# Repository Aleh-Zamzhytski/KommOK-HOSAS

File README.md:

# HOSAS Joystick Set

[Русская версия](#ru) · English

Two-stick controller set (HOSAS — Hands On Stick And Stick) for space flight simulators.
Eight analog axes: six for ship motion, two for camera control. Grips are 3D-printed,
boards are single-sided and suitable for home fabrication by the laser toner transfer
method (LTTM), controllers are STM32 Blue Pill or Arduino Pro Micro.

This document is the current build reference. Separate assembly documentation does not
exist yet; unfinished items are marked `TODO` and listed in [Known gaps](#known-gaps).

Video review (original sound in Russian): `TODO — YouTube link`

---

## 1. Overview

| Input | Axes | Buttons |
|---|---|---|
| Right grip | 4 | 2 |
| Left grip | 4 | 2 |

| Parameter | Value |
|---|---|
| Controller, current build | STM32 Blue Pill (STM32F103C8T6), USB Custom HID |
| Controller, earlier builds | Arduino Pro Micro (ATmega32U4), supported |
| Axis sensing | Potentiometers → ADC (DMA on STM32) |
| Centering | Return spring |
| Fastening | Wood screws into printed bosses |
| Host interface | USB, no driver installation |
| Desk mount | Welded 20×20 / 15×15 mm steel tube, M8 bolts |

## 2. Repository layout

```
body/                               3D models and print layouts
  Joystick_Base_v0.4.f3d / .step        base, editable source + STEP
  joystick_handle_v0.6.f3d / .step      grip, editable source + STEP
  Base_Print_Layout.3mf                 slicer project, base parts
  Left_Handle_Print_Layout.3mf          slicer project, left grip
  Right_Handle_Print_Layout.3mf         slicer project, right grip
electronics/
  joystick_v4_left/                     KiCad project + joystick_v4-Cu.svg (copper artwork)
  joystick_v4_right/                    KiCad project + joystick_v4-Cu.svg (copper artwork)
firmware/
  Arduino/HOSAS/HOSAS.ino               Pro Micro sketch
  STM32/CJoy/                           STM32CubeIDE project (CJoy.ioc, Core, USB_DEVICE)
  STM32/prebuilt/CJoy.bin               compiled firmware, flash-ready
BOM.md                                Bill of materials
```

One KiCad project per hand. Editable CAD is Fusion 360 (`.f3d`); `.step` is provided for
other CAD systems. STL files are not published — export from the STEP.

## 3. Parts and tools

Bill of materials: [BOM.md](BOM.md).

Tools: 3D printer; laser printer and glossy paper; iron; etching chemicals; carbide drill
bits; soldering iron and hot air; multimeter; crimp tool; ST-Link V2 for STM32 flashing.

## 4. Build

Sequence: print → PCB → assembly → firmware → verification. Test after each stage, not
after final assembly; faults are cheaper to find early.

### 4.1 Printing

Print the four slicer projects in `body/` — 2x base, left grip, right grip. Parts are already
arranged with supports. Scale 100 %: potentiometer seats and screw bosses are
dimension-critical.

| Parameter | Value |
|---|---|
| Material | eSun PLA+ |
| Nozzle | 0.4 |
| Slicer | Orca Slicer v2.4.1 |

### 4.2 PCB fabrication (LTTM)

**Current PCB design is for STM32 only.**
`TODO add Arduino Pro Micro PCB design`
Artwork: `electronics/joystick_v4_*/joystick_v4-Cu.svg` (copper layer).
Project files: `.kicad_pro`, `.kicad_sch`, `.kicad_pcb` — KiCad 9.0.

Home fabrication is recommended for a first prototype: a fab-house order adds weeks of
lead time before a layout error becomes apparent.

1. **Print the artwork** on glossy paper with a laser printer, **it is already mirrored**, at 1:1 scale.
   Verify the scale against a known 2.54 mm header pitch before transfer.
2. **Prepare the laminate:** wet 1000-grit abrasive, then degrease with alcohol.
3. **Transfer:** iron near maximum (cotton setting), toner side down, about two minutes
   with firm, even pressure.
4. **Remove the paper:** soak in hot soapy water for 30 minutes, then roll the paper off
   with the fingers under water. Toner remaining on copper indicates the correct
   temperature; smeared toner means too hot, toner left on paper means too cold.
5. **Etch:** 100 ml hydrogen peroxide + 30 g citric acid + 5 g sodium chloride. Keep the
   vessel on a water bath or other mild heat source and agitate periodically. Clearing of
   the copper between tracks takes 20–30 minutes.
6. **Finish:** strip the toner with fine abrasive, drill with carbide bits (standard bits
   tear the tracks), trim the board to size.
7. **Tin and solder:** rosin or no-clean flux only; acid fluxes are not acceptable.
   Through-hole components from the solder side, SMD on the component side with hot air.
   A double-sided board is made as two single-sided boards joined by wire links.
8. **Verify:** check every track for continuity and every adjacent pair for shorts with a
   multimeter. Use crimped DuPont connectors for detachable wiring.

Read [Safety](#5-safety) before etching.

### 4.3 Mechanical assembly

Detailed instructions: `TODO`. Current sequence:

1. Mount the potentiometers in their designed seats and check alignment over the full
   travel of each axis before fixing them.
2. Fasten the boards and mechanical parts with wood screws into the printed bosses.
   Plastic threads tolerate limited torque; overtightening breaks them.
3. Fit the return spring under tension. Confirm free travel and reliable centering of
   both axes before closing the grip.
4. Wire the axes and buttons according to the schematic, then verify direction and
   endpoint values on the host before final closure.

### 4.4 Firmware

**Arduino Pro Micro** — `firmware/Arduino/HOSAS/HOSAS.ino`

Open the sketch in Arduino IDE, select board `Arduino Micro`, install 
https://github.com/MHeironimus/ArduinoJoystickLibrary, upload, then verify in the host joystick panel.

**STM32 Blue Pill** — `firmware/STM32/CJoy/`

STM32CubeIDE project generated from `CJoy.ioc`. Target STM32F103C8Tx, linker script
`STM32F103C8TX_FLASH.ld`. USB class: Custom HID; the report descriptor is defined in
`USB_DEVICE/App/usbd_custom_hid_if.c`. Axes are read by ADC with DMA
(`Core/Src/adc.c`, `Core/Src/dma.c`), buttons through GPIO.

- Build: import the project into STM32CubeIDE and build.
- Flash without building: `firmware/STM32/prebuilt/CJoy.bin`.
- Upload: ST-Link V2 over SWD (SWDIO, SWCLK, GND, 3V3), or the factory USART1 bootloader
  with BOOT0 = 1 using STM32CubeProgrammer. Flash address `0x08000000`.
- Axis limits, inversion, and deadzone: `TODO — document the constants in Core/Src/main.c`.

The Blue Pill costs about half as much as the Pro Micro and offers higher performance;
the flashing procedure is more involved.

### 4.5 Verification and binding

1. Confirm that both sticks enumerate as separate USB devices.
2. Open the host joystick panel (Windows: `joy.cpl`) and check all axes and all
   buttons: full range, stable center, no jitter, correct direction.
3. Assign the axes in the simulator, invert where required, apply a deadzones,
   and set response curves for the translation axes.

## 5. Safety

Respiratory and eye protection are required when abrading copper laminate and when
etching; work in a ventilated area. Welding and abrasive cutting require the corresponding
protective equipment.

Spent etchant must not be discharged into the drain. Neutralise it with iron filings or
steel offcuts; decant only the clear liquid after neutralisation and dispose of the solid
residue as household waste.

The project is provided "as is", without warranty. Fabrication and use are undertaken at
the operator's own risk.

## 6. Desk mount

The mount holds the grip at elbow height and leaves the keyboard and mouse area free.
Construction: 20×20 and 15×15 mm steel tube, cut, welded, roller-painted, with felt pads on
all desk contact surfaces to prevent slipping and scratching.

Cut list and drawings: `TODO — not published yet`.

## Known gaps

- Step-by-step mechanical assembly instructions.
- Desk mount cut list and drawings.
- Third-revision defects and planned changes.

Corrections and additions are welcome through Issues.

## License

| Scope | License |
|---|---|
| Firmware (`firmware/`) | Apache License 2.0 |
| CAD models, PCB designs, documentation, media | CC BY 4.0 |

Copying, modification, and redistribution, including commercial use, are permitted.
Firmware redistribution requires retention of the LICENSE and NOTICE files and a notice
stating that files were modified. Redistribution of design files requires credit, a link
to this repository, a link to the license, and an indication of changes.

> Based on the HOSAS Joystick project by Aleh-Zamzhytski and Kommande —
> https://github.com/Aleh-Zamzhytski/KommOK-HOSAS (hardware: CC BY 4.0, firmware: Apache-2.0).

Attribution on physical builds, photographs, and videos is appreciated but not required.
Third-party components under `firmware/STM32/CJoy/Drivers` and `Middlewares` retain their
own licenses (see the `LICENSE.txt` files in those directories).

---

## Комплект HOSAS Джойстиков

[English version](#hosas-joystick-set) · Русский

Комплект из двух джойстиков (HOSAS — Hands On Stick And Stick) для космических
симуляторов. Восемь аналоговых осей: шесть на движение корабля, две на камеру.
Рукояти печатаются на 3D-принтере, платы односторонние и изготавливаются дома по
лазерно-утюжной технологии (ЛУТ), контроллеры — STM32 Blue Pill или Arduino Pro Micro.

Видеообзор: `TODO — ссылка на YouTube`

Раздел повторяет английскую версию выше. При расхождении актуальна английская.

### 1. Обзор

| Орган управления | Оси | Кнопки |
|---|---|---|
| Правый джойстик | 4 | 2 |
| Левый джойстик | 4 | 2 |

| Параметр | Значение |
|---|---|
| Контроллер, текущая версия | STM32 Blue Pill (STM32F103C8T6), USB Custom HID |
| Контроллер, ранние версии | Arduino Pro Micro (ATmega32U4), поддерживается |
| Оси | Потенциометры → АЦП (DMA на STM32) |
| Возврат в центр | Возвратная пружина |
| Крепёж | Саморезы по дереву в печатные колодцы |
| Интерфейс | USB, установка драйверов не требуется |
| Крепление к столу | Сварная профильная труба 20×20 / 15×15 мм, болты М8 |

### 2. Файлы репозитория

Структура приведена в [английском разделе](#2-repository-layout): имена файлов и каталогов
от языка не зависят.

Один проект KiCad на каждую руку. Редактируемые модели — Fusion 360 (`.f3d`), `.step`
предоставлен для других CAD-систем. STL можно получить экспортом из STEP.

### 3. Детали и инструмент

Спецификация деталей: [BOM.md](BOM.md).

Инструмент: 3D-принтер; лазерный принтер и глянцевая бумага; утюг; реактивы для травления;
свёрла из карбида вольфрама; паяльник и фен; мультиметр; кримпер; ST-Link V2 для прошивки STM32.

### 4. Сборка

Последовательность: печать → плата → сборка → прошивка → проверка. Контроль выполняется
после каждого этапа, а не после окончательной сборки: так дефекты обходятся дешевле.

#### 4.1 Печать

Печатаются четыре набора деталей из трёх файлов в `body/`: база — дважды (по одной на
каждый джойстик), левый джойстик, правый джойстик. Детали уже расставлены с поддержками.
Масштаб 100 %: посадочные места потенциометров и колодцы под саморезы критичны к размерам.

| Параметр | Значение |
|---|---|
| Материал | eSun PLA+ |
| Сопло | 0,4 мм |
| Слайсер | Orca Slicer v2.4.1 |

#### 4.2 Изготовление платы (ЛУТ)

Текущая разводка рассчитана только на STM32. `TODO — добавить плату под Arduino Pro Micro`

Картинка для перевода на текстолит: `electronics/joystick_v4_*/joystick_v4-Cu.svg`.
Файлы проекта: `.kicad_pro`, `.kicad_sch`, `.kicad_pcb` — KiCad 9.0.

Для первого прототипа рекомендуется домашнее изготовление: заказ на фабрике добавляет
недели ожидания, прежде чем обнаружится ошибка в разводке.

1. **Печать рисунка** на глянцевой бумаге лазерным принтером, масштаб 1:1.
   Рисунок **уже отзеркален**, повторно зеркалить не нужно. Перед переносом проверить
   масштаб по заведомо известному шагу выводов 2,54 мм.
2. **Подготовка текстолита:** мокрая наждачная бумага P1000, затем обезжиривание IPA спиртом.
3. **Перенос:** утюг почти на максимум (режим «хлопок»), тонером вниз, около двух минут
   с равномерным прижимом.
4. **Снятие бумаги:** замачивание в горячей воде с мылом на 30 минут, затем скатывание
   бумаги пальцами под водой. Тонер остался на меди — температура выбрана верно;
   расплылся — утюг перегрет; остался на бумаге — недогрет.
5. **Травление:** 100 мл перекиси водорода + 30 г лимонной кислоты + 5 г поваренной соли.
   Ёмкость на водяной бане или другом слабом нагреве, периодически помешивать.
   Медь между дорожками уходит за 20–30 минут.
6. **Финиш:** снять тонер мелкой наждачкой, сверлить карбидным сверлом (обычное рвёт
   дорожки), обрезать плату по размеру.
7. **Лужение и пайка:** только канифоль или безотмывочный флюс; кислотные флюсы
   недопустимы. DIP-компоненты — с обратной стороны, SMD — феном с лицевой.
   Двусторонняя плата изготавливается как две односторонние, соединённые проволочными
   перемычками.
8. **Контроль:** прозвонить мультиметром каждую дорожку на обрыв и каждую соседнюю пару
   на замыкание. Разъёмные соединения — обжатые контакты DuPont.

Перед травлением прочитать [раздел 5](#5-безопасность).

#### 4.3 Механическая сборка

Подробная инструкция: `TODO`. Текущая последовательность:

1. Установить потенциометры в посадочные места и проверить показания для каждой оси до окончательного крепления.
2. Крепить платы и механику саморезами по дереву в печатные колодцы. Резьба в пластике
   держит ограниченный момент; перетяжка её срывает.
3. Установить возвратную пружину с натягом. До финальной сборки рукояти убедиться в свободном
   ходе и надёжном возврате обеих осей в центр.
4. Развести оси и кнопки по схеме, затем проверить направление и крайние значения
   на компьютере.

#### 4.4 Прошивка

**Arduino Pro Micro** — `firmware/Arduino/HOSAS/HOSAS.ino`

Открыть скетч в Arduino IDE, выбрать плату `Arduino Micro`, установить библиотеку
[ArduinoJoystickLibrary](https://github.com/MHeironimus/ArduinoJoystickLibrary),
загрузить, проверить в панели игровых устройств.

**STM32 Blue Pill** — `firmware/STM32/CJoy/`

Проект STM32CubeIDE, сгенерированный из `CJoy.ioc`. Плата STM32F103C8Tx, linker script
`STM32F103C8TX_FLASH.ld`. Класс USB — Custom HID; дескриптор отчёта задан в
`USB_DEVICE/App/usbd_custom_hid_if.c`. Оси читаются АЦП с DMA (`Core/Src/adc.c`,
`Core/Src/dma.c`), кнопки — через GPIO.

- Сборка: импортировать проект в STM32CubeIDE и собрать.
- Прошивка без сборки: `firmware/STM32/prebuilt/CJoy.bin`.
- Загрузка: ST-Link V2 по SWD (SWDIO, SWCLK, GND, 3V3) либо штатный загрузчик USART1
  при BOOT0 = 1 через STM32CubeProgrammer. Адрес `0x08000000`.
- Пределы осей, инверсия и мёртвая зона: `TODO — описать константы в Core/Src/main.c`.

Blue Pill примерно вдвое дешевле Pro Micro при большей производительности; процедура
прошивки сложнее.

#### 4.5 Проверка и назначение осей

1. Убедиться, что оба джойстика определяются как отдельные USB-устройства.
2. Открыть панель игровых устройств (Windows: `joy.cpl`) и проверить все оси и кнопки:
   полный диапазон, устойчивый центр, отсутствие дрожания, верное направление.
3. Назначить оси в симуляторе, при необходимости инвертировать, задать мёртвые зоны
   и кривые отклика для осей смещения.

### 5. Безопасность

При зачистке текстолита и травлении обязательны респиратор и защитные очки; работать
в проветриваемом помещении. Сварка и абразивная резка требуют соответствующих средств
защиты.

Отработанный раствор не сливается в канализацию. Он нейтрализуется железными опилками
или стальными обрезками; после нейтрализации сливается только прозрачная жидкость,
твёрдый остаток утилизируется как бытовой отход.

Проект предоставляется «как есть», без гарантий. Изготовление и использование —
на риск исполнителя.

### 6. Крепление к столу

Крепление удерживает рукоять на уровне локтя и оставляет свободными место на столе для клавиатуры и мыши.
Конструкция: профильная труба 20×20 и 15×15 мм, резка, сварка, окраска валиком,
войлочные накладки на всех площадках, касающихся стола, — против скольжения и царапин.
Крепление изготавливается отдельно для каждого джойстика.

Раскрой и чертежи: `TODO — ещё не опубликованы`.

### Известные пробелы

- Пошаговая инструкция по механической сборке.
- Раскрой и чертежи крепления к столу.
- Дефекты третьей ревизии и планируемые изменения.

Исправления и дополнения принимаются через Issues.

### Лицензия

| Область | Лицензия |
|---|---|
| Прошивка (`firmware/`) | Apache License 2.0 |
| 3D-модели, платы, документация, медиа | CC BY 4.0 |

Копирование, изменение и распространение, включая коммерческое использование, разрешены.
При распространении прошивки обязательны сохранение файлов LICENSE и NOTICE и указание
на внесённые изменения. При распространении файлов конструкции обязательны указание
авторства, ссылка на репозиторий, ссылка на лицензию и отметка об изменениях.
Полные условия — в [английском разделе](#license).

> Based on the HOSAS Joystick project by Aleh-Zamzhytski and Kommande —
> https://github.com/Aleh-Zamzhytski/KommOK-HOSAS (hardware: CC BY 4.0, firmware: Apache-2.0).

Указание авторства на физических сборках, фотографиях и видео приветствуется,
но не обязательно.

Сторонние компоненты в `firmware/STM32/CJoy/Drivers` и `Middlewares` сохраняют
собственные лицензии (см. файлы `LICENSE.txt` в этих каталогах).

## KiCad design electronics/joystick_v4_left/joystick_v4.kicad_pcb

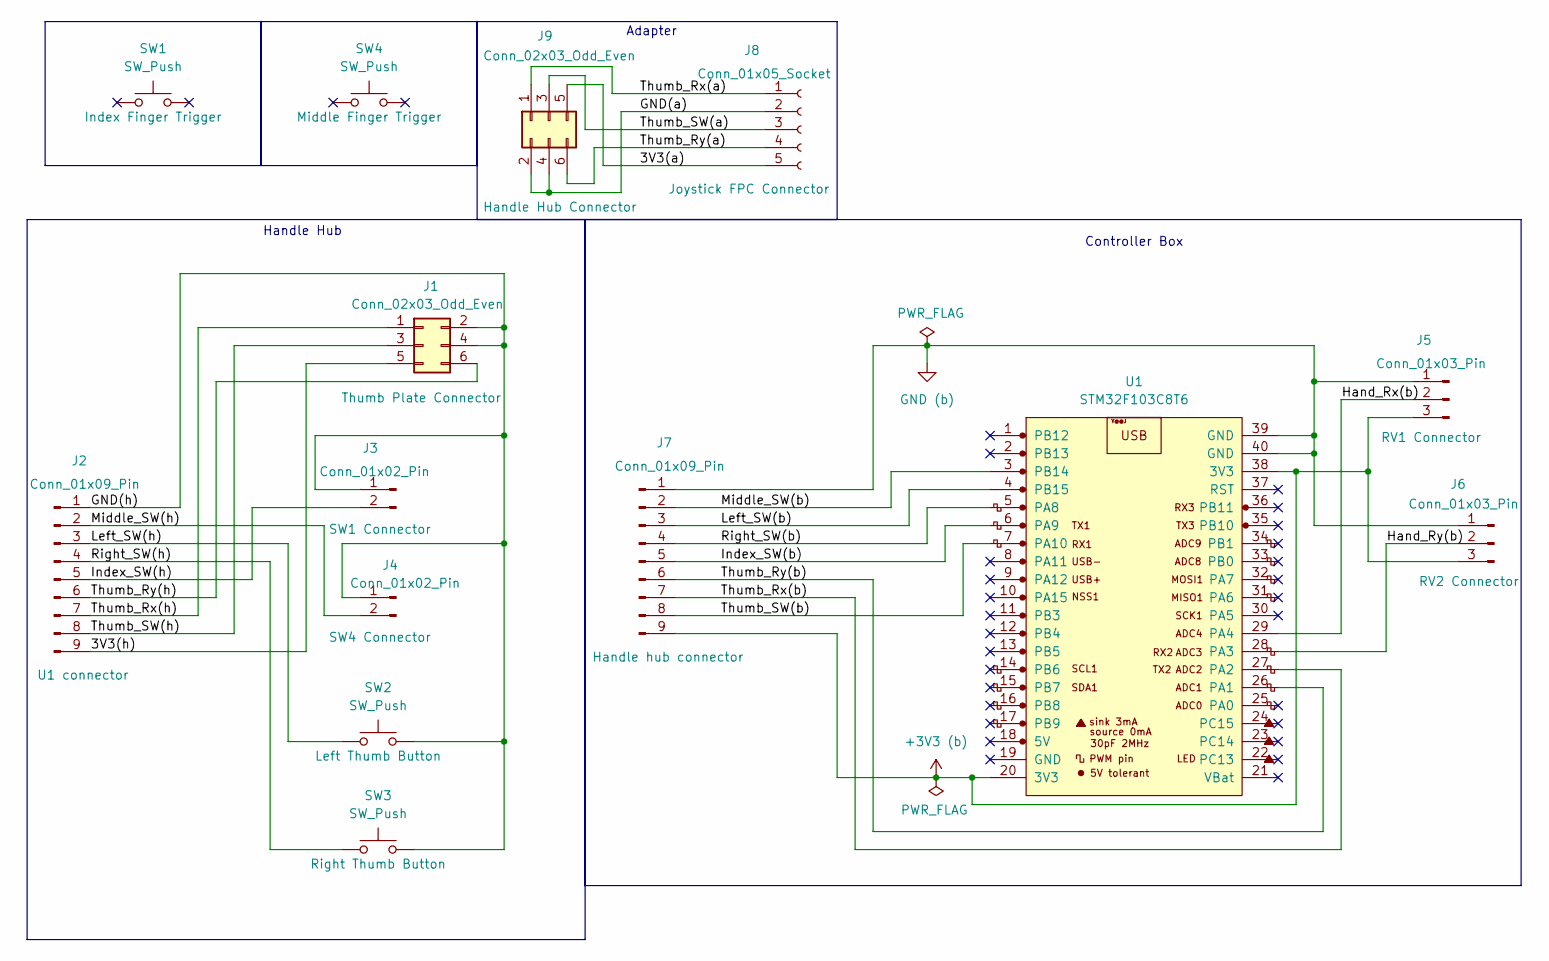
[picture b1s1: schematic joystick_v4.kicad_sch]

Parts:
J1, J9: Conn_02x03_Odd_Even; PinHeader_2x03_P2.54mm_Vertical
J2, J7: Conn_01x09_Pin; PinHeader_1x09_P2.54mm_Vertical
J3, J4: Conn_01x02_Pin; PinHeader_1x02_P2.54mm_Vertical
J5, J6: Conn_01x03_Pin; PinHeader_1x03_P2.54mm_Vertical
J8: Conn_01x05_Socket; TE_0-1734839-5_1x05-1MP_P0.5mm_Horizontal
SW1, SW2, SW3, SW4: SW_Push; SW_PUSH_6mm_H5mm
U1: STM32F103C8T6; YAAJ_BluePill_1

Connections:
+3V3 (b): J5.3, J6.3, J7.9, U1.20 (3V3), U1.38 (3V3)
/3V3(a): J8.5, J9.5
/3V3(h): J1.5, J2.9
/GND(a): J8.2, J9.2, J9.4
/GND(h): J1.2, J1.4, J2.1, J3.1, J4.1, SW2.2, SW3.2
/Hand_Rx(b): J5.2, U1.29 (PA4)
/Hand_Ry(b): J6.2, U1.28 (PA3)
/Index_SW(b): J7.5, U1.6 (PA9)
/Index_SW(h): J2.5, J3.2
/Left_SW(b): J7.3, U1.4 (PB15)
/Left_SW(h): J2.3, SW2.1
/Middle_SW(b): J7.2, U1.3 (PB14)
/Middle_SW(h): J2.2, J4.2
/Right_SW(b): J7.4, U1.5 (PA8)
/Right_SW(h): J2.4, SW3.1
/Thumb_Rx(a): J8.1, J9.1
/Thumb_Rx(b): J7.7, U1.27 (PA2)
/Thumb_Rx(h): J1.1, J2.7
/Thumb_Ry(a): J8.4, J9.6
/Thumb_Ry(b): J7.6, U1.26 (PA1)
/Thumb_Ry(h): J1.6, J2.6
/Thumb_SW(a): J8.3, J9.3
/Thumb_SW(b): J7.8, U1.7 (PA10)
/Thumb_SW(h): J1.3, J2.8
GND (b): J5.1, J6.1, J7.1, U1.39 (GND), U1.40 (GND)

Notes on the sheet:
Handle Hub
Controller Box
Adapter

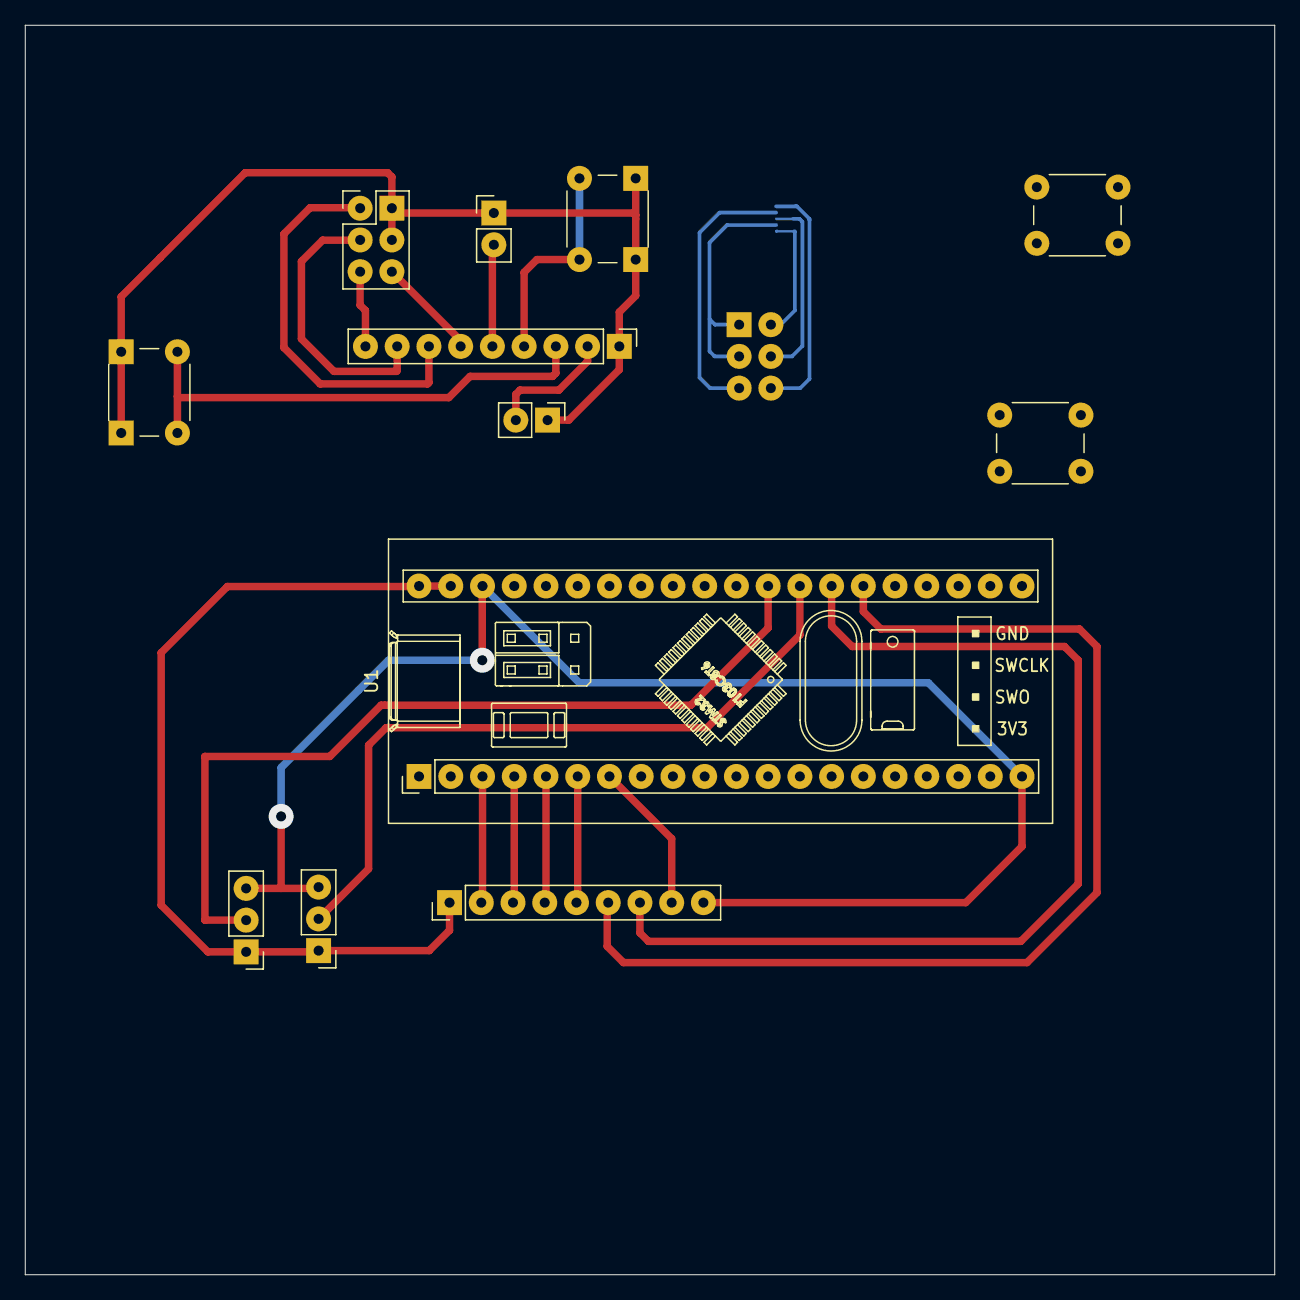
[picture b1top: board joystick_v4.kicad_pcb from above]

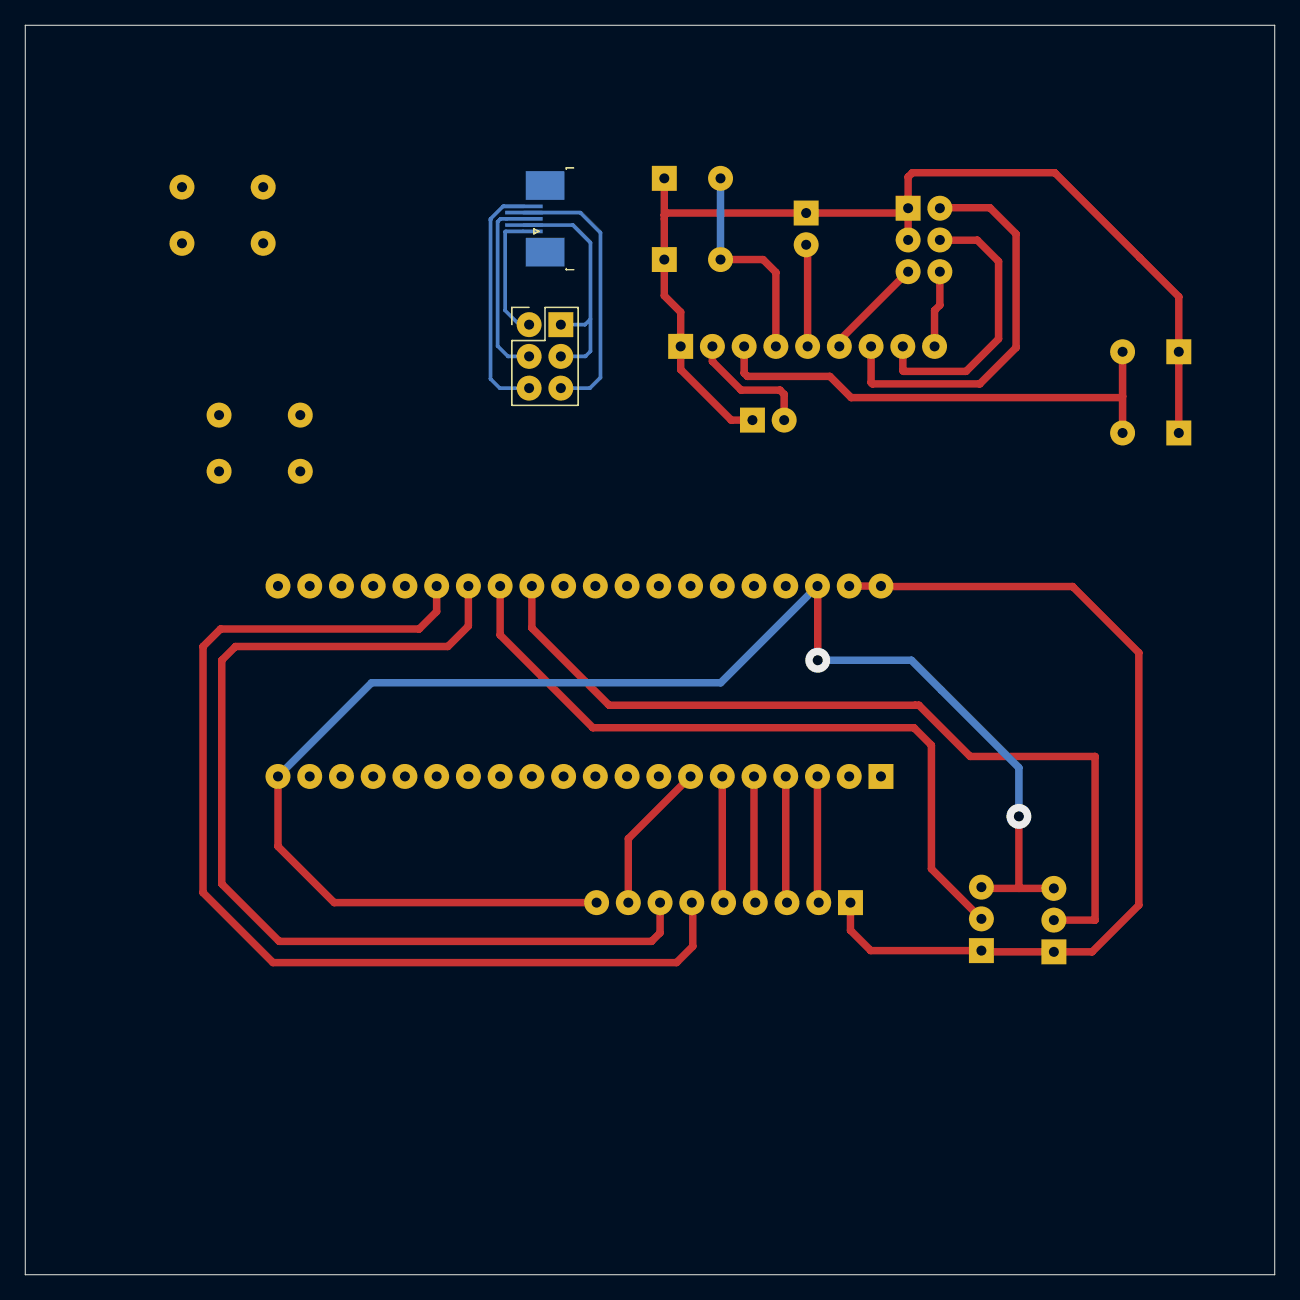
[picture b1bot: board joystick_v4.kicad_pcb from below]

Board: 2 copper layers, 100.0 x 100.0 mm, 14 parts (2 on the bottom side), 25 nets.

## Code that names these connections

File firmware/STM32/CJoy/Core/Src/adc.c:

/* USER CODE BEGIN Header */
/**
  ******************************************************************************
  * @file    adc.c
  * @brief   This file provides code for the configuration
  *          of the ADC instances.
  ******************************************************************************
  * @attention
  *
  * Copyright (c) 2025 STMicroelectronics.
  * All rights reserved.
  *
  * This software is licensed under terms that can be found in the LICENSE file
  * in the root directory of this software component.
  * If no LICENSE file comes with this software, it is provided AS-IS.
  *
  ******************************************************************************
  */
/* USER CODE END Header */
/* Includes ------------------------------------------------------------------*/
#include "adc.h"

/* USER CODE BEGIN 0 */
volatile uint16_t adc_dma_buffer[ADC_BUFFER_SIZE];
volatile uint32_t adc_filtered_values[ADC_CHANNELS] = {0};
volatile uint8_t adc_data_ready = 0;

typedef struct
{
  uint16_t buffer[FILTER_WINDOW];
  uint8_t index;
  uint32_t sum;
} MovingAverageFilter;

MovingAverageFilter adc_filters[ADC_CHANNELS] = {0};

void ADC_Filter_Init(void)
{
  for (int ch = 0; ch < ADC_CHANNELS; ch++)
  {
    for (int i = 0; i < FILTER_WINDOW; i++)
    {
      adc_filters[ch].buffer[i] = 0;
    }
    adc_filters[ch].index = 0;
    adc_filters[ch].sum = 0;
  }
}

uint16_t ADC_Apply_Moving_Average(uint8_t channel, uint16_t new_value)
{
  MovingAverageFilter *filter = &adc_filters[channel];

  filter->sum -= filter->buffer[filter->index];
  filter->buffer[filter->index] = new_value;
  filter->sum += new_value;

  filter->index = (filter->index + 1) % FILTER_WINDOW;

  return (uint16_t)(filter->sum / FILTER_WINDOW);
}

void ADC_Start_DMA_Conversion(void)
{
  ADC_Filter_Init();
  if (HAL_ADC_Start_DMA(&hadc1, (uint32_t *)adc_dma_buffer, ADC_BUFFER_SIZE) != HAL_OK)
  {
    Error_Handler();
  }
}

uint16_t ADC_GetFilteredValue(uint8_t channel)
{
  if (channel < ADC_CHANNELS)
  {
    return (uint16_t)adc_filtered_values[channel];
  }
  return 0;
}


void HAL_ADC_ConvHalfCpltCallback(ADC_HandleTypeDef *hadc)
{
  if (hadc->Instance == ADC1)
  {
    for (int i = 0; i < ADC_BUFFER_SIZE / 2; i += ADC_CHANNELS)
    {
      for (int ch = 0; ch < ADC_CHANNELS; ch++)
      {
        uint16_t raw_value = adc_dma_buffer[i + ch];
        uint16_t filtered = ADC_Apply_Moving_Average(ch, raw_value);
        adc_filtered_values[ch] = filtered;
      }
    }
  }
}

void HAL_ADC_ConvCpltCallback(ADC_HandleTypeDef *hadc)
{
  if (hadc->Instance == ADC1)
  {

    for (int i = ADC_BUFFER_SIZE / 2; i < ADC_BUFFER_SIZE; i += ADC_CHANNELS)
    {
      for (int ch = 0; ch < ADC_CHANNELS; ch++)
      {
        uint16_t raw_value = adc_dma_buffer[i + ch];
        uint16_t filtered = ADC_Apply_Moving_Average(ch, raw_value);
        adc_filtered_values[ch] = filtered;
      }
    }
    adc_data_ready = 1;
  }
}
/* USER CODE END 0 */

ADC_HandleTypeDef hadc1;
DMA_HandleTypeDef hdma_adc1;

/* ADC1 init function */
void MX_ADC1_Init(void)
{

  /* USER CODE BEGIN ADC1_Init 0 */

  /* USER CODE END ADC1_Init 0 */

  ADC_ChannelConfTypeDef sConfig = {0};

  /* USER CODE BEGIN ADC1_Init 1 */

  /* USER CODE END ADC1_Init 1 */

  /** Common config
  */
  hadc1.Instance = ADC1;
  hadc1.Init.ScanConvMode = ADC_SCAN_ENABLE;
  hadc1.Init.ContinuousConvMode = ENABLE;
  hadc1.Init.DiscontinuousConvMode = DISABLE;
  hadc1.Init.ExternalTrigConv = ADC_SOFTWARE_START;
  hadc1.Init.DataAlign = ADC_DATAALIGN_RIGHT;
  hadc1.Init.NbrOfConversion = 4;

  if (HAL_ADC_Init(&hadc1) != HAL_OK)
  {
    Error_Handler();
  }

  /** Configure Regular Channel
  */
  sConfig.Channel = ADC_CHANNEL_1;
  sConfig.Rank = ADC_REGULAR_RANK_1;
  sConfig.SamplingTime = ADC_SAMPLETIME_239CYCLES_5;
  if (HAL_ADC_ConfigChannel(&hadc1, &sConfig) != HAL_OK)
  {
    Error_Handler();
  }

  /** Configure Regular Channel
  */
  sConfig.Channel = ADC_CHANNEL_2;
  sConfig.Rank = ADC_REGULAR_RANK_2;
  sConfig.SamplingTime = ADC_SAMPLETIME_239CYCLES_5;
  if (HAL_ADC_ConfigChannel(&hadc1, &sConfig) != HAL_OK)
  {
    Error_Handler();
  }

  /** Configure Regular Channel
  */
  sConfig.Channel = ADC_CHANNEL_3;
  sConfig.Rank = ADC_REGULAR_RANK_3;
  sConfig.SamplingTime = ADC_SAMPLETIME_239CYCLES_5;
  if (HAL_ADC_ConfigChannel(&hadc1, &sConfig) != HAL_OK)
  {
    Error_Handler();
  }

  /** Configure Regular Channel
  */
  sConfig.Channel = ADC_CHANNEL_4;
  sConfig.Rank = ADC_REGULAR_RANK_4;
  sConfig.SamplingTime = ADC_SAMPLETIME_239CYCLES_5;
  if (HAL_ADC_ConfigChannel(&hadc1, &sConfig) != HAL_OK)
  {
    Error_Handler();
  }
  /* USER CODE BEGIN ADC1_Init 2 */

  /* USER CODE END ADC1_Init 2 */

}

void HAL_ADC_MspInit(ADC_HandleTypeDef* adcHandle)
{

  GPIO_InitTypeDef GPIO_InitStruct = {0};
  if(adcHandle->Instance==ADC1)
  {
  /* USER CODE BEGIN ADC1_MspInit 0 */

  /* USER CODE END ADC1_MspInit 0 */
    /* ADC1 clock enable */
    __HAL_RCC_ADC1_CLK_ENABLE();

    __HAL_RCC_GPIOA_CLK_ENABLE();
    /**ADC1 GPIO Configuration
    PA1     ------> ADC1_IN1
    PA2     ------> ADC1_IN2
    PA3     ------> ADC1_IN3
    PA4     ------> ADC1_IN4
    */
    GPIO_InitStruct.Pin = X_Axis_Pin|Y_Axis_Pin|Z_Axis_Pin|RX_Axis_Pin;
    GPIO_InitStruct.Mode = GPIO_MODE_ANALOG;
    HAL_GPIO_Init(GPIOA, &GPIO_InitStruct);

    /* ADC1 DMA Init */
    /* ADC1 Init */
    hdma_adc1.Instance = DMA1_Channel1;
    hdma_adc1.Init.Direction = DMA_PERIPH_TO_MEMORY;
    hdma_adc1.Init.PeriphInc = DMA_PINC_DISABLE;
    hdma_adc1.Init.MemInc = DMA_MINC_ENABLE;
    hdma_adc1.Init.PeriphDataAlignment = DMA_PDATAALIGN_HALFWORD;
    hdma_adc1.Init.MemDataAlignment = DMA_MDATAALIGN_HALFWORD;
    hdma_adc1.Init.Mode = DMA_CIRCULAR;
    hdma_adc1.Init.Priority = DMA_PRIORITY_HIGH;
    if (HAL_DMA_Init(&hdma_adc1) != HAL_OK)
    {
      Error_Handler();
    }

    __HAL_LINKDMA(adcHandle,DMA_Handle,hdma_adc1);

  /* USER CODE BEGIN ADC1_MspInit 1 */

  /* USER CODE END ADC1_MspInit 1 */
  }
}

void HAL_ADC_MspDeInit(ADC_HandleTypeDef* adcHandle)
{

  if(adcHandle->Instance==ADC1)
  {
  /* USER CODE BEGIN ADC1_MspDeInit 0 */

  /* USER CODE END ADC1_MspDeInit 0 */
    /* Peripheral clock disable */
    __HAL_RCC_ADC1_CLK_DISABLE();

    /**ADC1 GPIO Configuration
    PA1     ------> ADC1_IN1
    PA2     ------> ADC1_IN2
    PA3     ------> ADC1_IN3
    PA4     ------> ADC1_IN4
    */
    HAL_GPIO_DeInit(GPIOA, X_Axis_Pin|Y_Axis_Pin|Z_Axis_Pin|RX_Axis_Pin);

    /* ADC1 DMA DeInit */
    HAL_DMA_DeInit(adcHandle->DMA_Handle);
  /* USER CODE BEGIN ADC1_MspDeInit 1 */

  /* USER CODE END ADC1_MspDeInit 1 */
  }
}

/* USER CODE BEGIN 1 */

/* USER CODE END 1 */
